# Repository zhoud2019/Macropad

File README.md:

# Macropad

A compact 9-key macropad with 2 rotary encoders, programmed with QMK firmware. I built this project to challenge myself and gain hands-on experience with PCB design, firmware configuration, and hardware assembly, serving as a foundation for more advanced future projects, such as designing a miniature fan in the shape of a plane engine.

The macropad is designed as a programmable input device suitable for shortcuts, media control, and custom workflows.

---

## Overview

---

## Schematic

The schematic shows the wiring between the Seeed XIAO RP2040 microcontroller, the 3×3 switch matrix with 1N4148 diodes, and the two EC11 rotary encoders.

---

## PCB Design

The PCB is a custom 2-layer board designed in KiCad. The switch matrix is arranged in a 3×3 grid with diodes for each key to prevent ghosting. The two rotary encoders are mounted at the top of the board on either side of the XIAO.

Front copper layer:

Back copper layer:

---

## Case Assembly

The enclosure is a 3D-printed case secured with M3 brass heat-set inserts and M3 × 16 mm screws. The case is designed to hold the PCB snugly while keeping the switches and encoders accessible from the top.

---

## Bill of Materials

| Component | Quantity | Part |
|---|---|---|
| Microcontroller | 1x | Seeed XIAO RP2040 |
| Mechanical Switches | 9x | MX-style switches |
| Keycaps | 9x | ABS Keycaps |
| Rotary Encoder | 2x | EC11 |
| Diodes | 9x | 1N4148 |
| Brass Heat-Set Inserts | 4x | M3 |
| Screws | 4x | M3 × 16 mm |
| PCB | 1x | Custom 2-layer PCB |
| Case | 1x | 3D-printed enclosure |

---

## Firmware

This macropad runs [QMK Firmware](https://qmk.fm/). The default keymap assigns keys 1–9 to the switch matrix. The left encoder controls page up/down and the right encoder controls volume up/down.

To flash the firmware:
1. Hold the **BOOT** button on the XIAO and plug it into your computer via USB
2. A drive called **RPI-RP2** will appear
3. Drag and drop `firmware.uf2` onto that drive
4. The drive will disappear and the macropad will reboot with the new firmware

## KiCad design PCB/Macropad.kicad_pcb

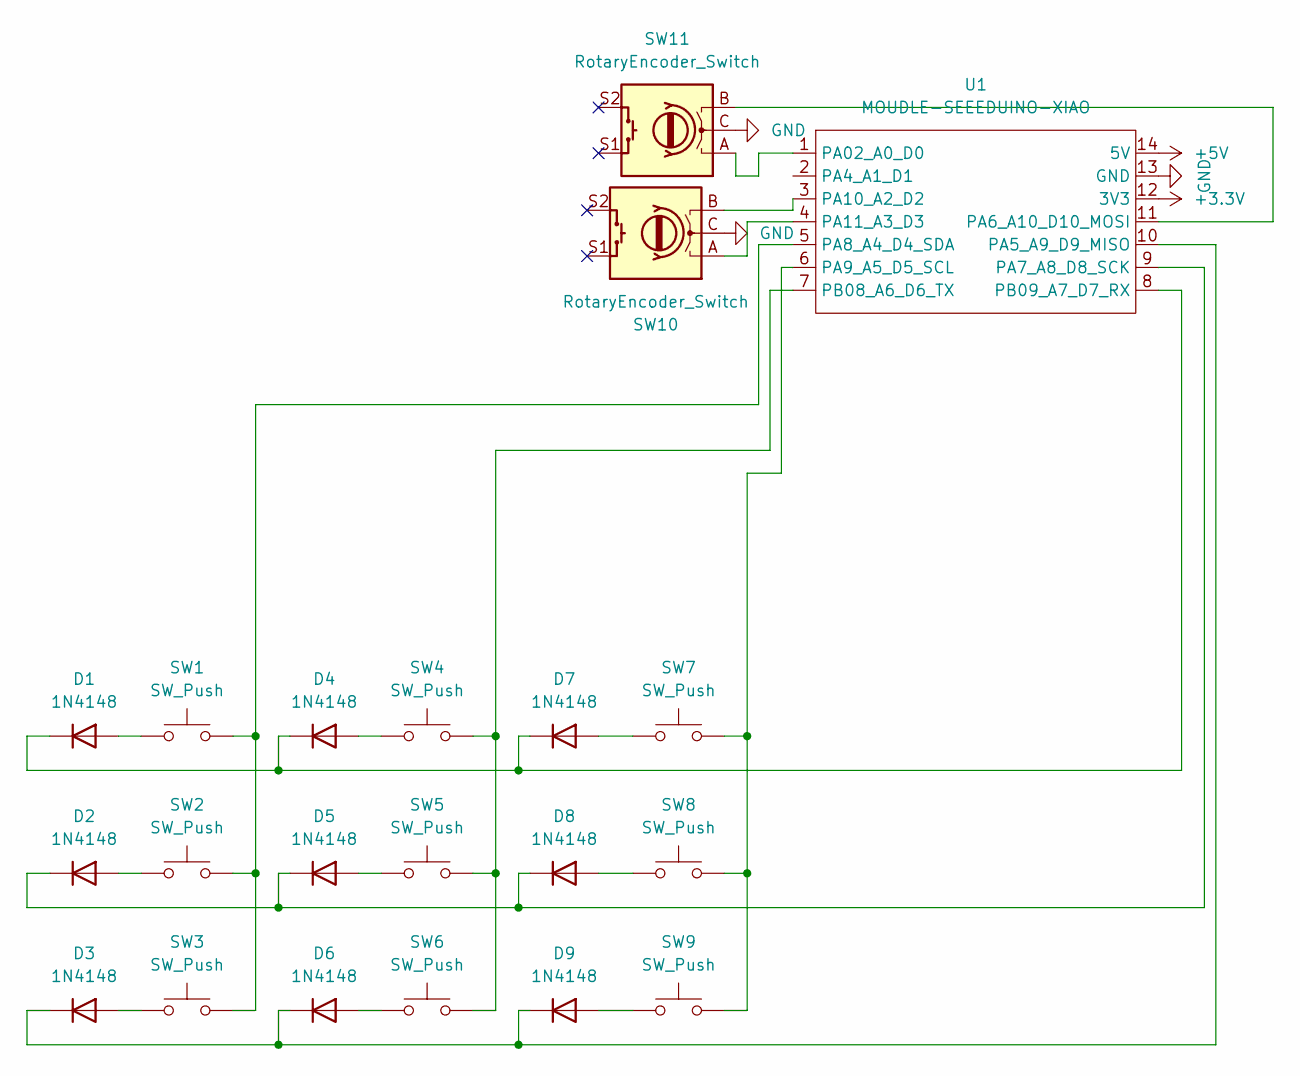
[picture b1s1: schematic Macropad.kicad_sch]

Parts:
D1, D2, D3, D4, D5, D6, D7, D8, D9: 1N4148; D_DO-35_SOD27_P7.62mm_Horizontal
SW1, SW2, SW3, SW4, SW5, SW6, SW7, SW8, SW9: SW_Push; SW_Cherry_MX_1.00u_PCB
SW10, SW11: RotaryEncoder_Switch; RotaryEncoder_Alps_EC11E-Switch_Vertical_H20mm
U1: MOUDLE-SEEEDUINO-XIAO; XIAO-Generic-Hybrid-14P-2.54-21X17.8MM

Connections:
+3.3V: U1.12 (3V3)
+5V: U1.14 (5V)
GND: SW10.C, SW11.C, U1.13 (GND)
unnamed: D1.2 (A), SW1.1
unnamed: D1.1 (K), D4.1 (K), D7.1 (K), U1.8 (PB09_A7_D7_RX)
unnamed: D2.2 (A), SW2.1
unnamed: D2.1 (K), D5.1 (K), D8.1 (K), U1.9 (PA7_A8_D8_SCK)
unnamed: D3.2 (A), SW3.1
unnamed: D3.1 (K), D6.1 (K), D9.1 (K), U1.10 (PA5_A9_D9_MISO)
unnamed: D4.2 (A), SW4.1
unnamed: D5.2 (A), SW5.1
unnamed: D6.2 (A), SW6.1
unnamed: D7.2 (A), SW7.1
unnamed: D8.2 (A), SW8.1
unnamed: D9.2 (A), SW9.1
unnamed: SW11.A, U1.1 (PA02_A0_D0)
unnamed: SW11.B, U1.11 (PA6_A10_D10_MOSI)
unnamed: SW1.2, SW2.2, SW3.2, U1.5 (PA8_A4_D4_SDA)
unnamed: SW7.2, SW8.2, SW9.2, U1.6 (PA9_A5_D5_SCL)
unnamed: SW10.B, U1.3 (PA10_A2_D2)
unnamed: SW10.A, U1.4 (PA11_A3_D3)
unnamed: SW4.2, SW5.2, SW6.2, U1.7 (PB08_A6_D6_TX)

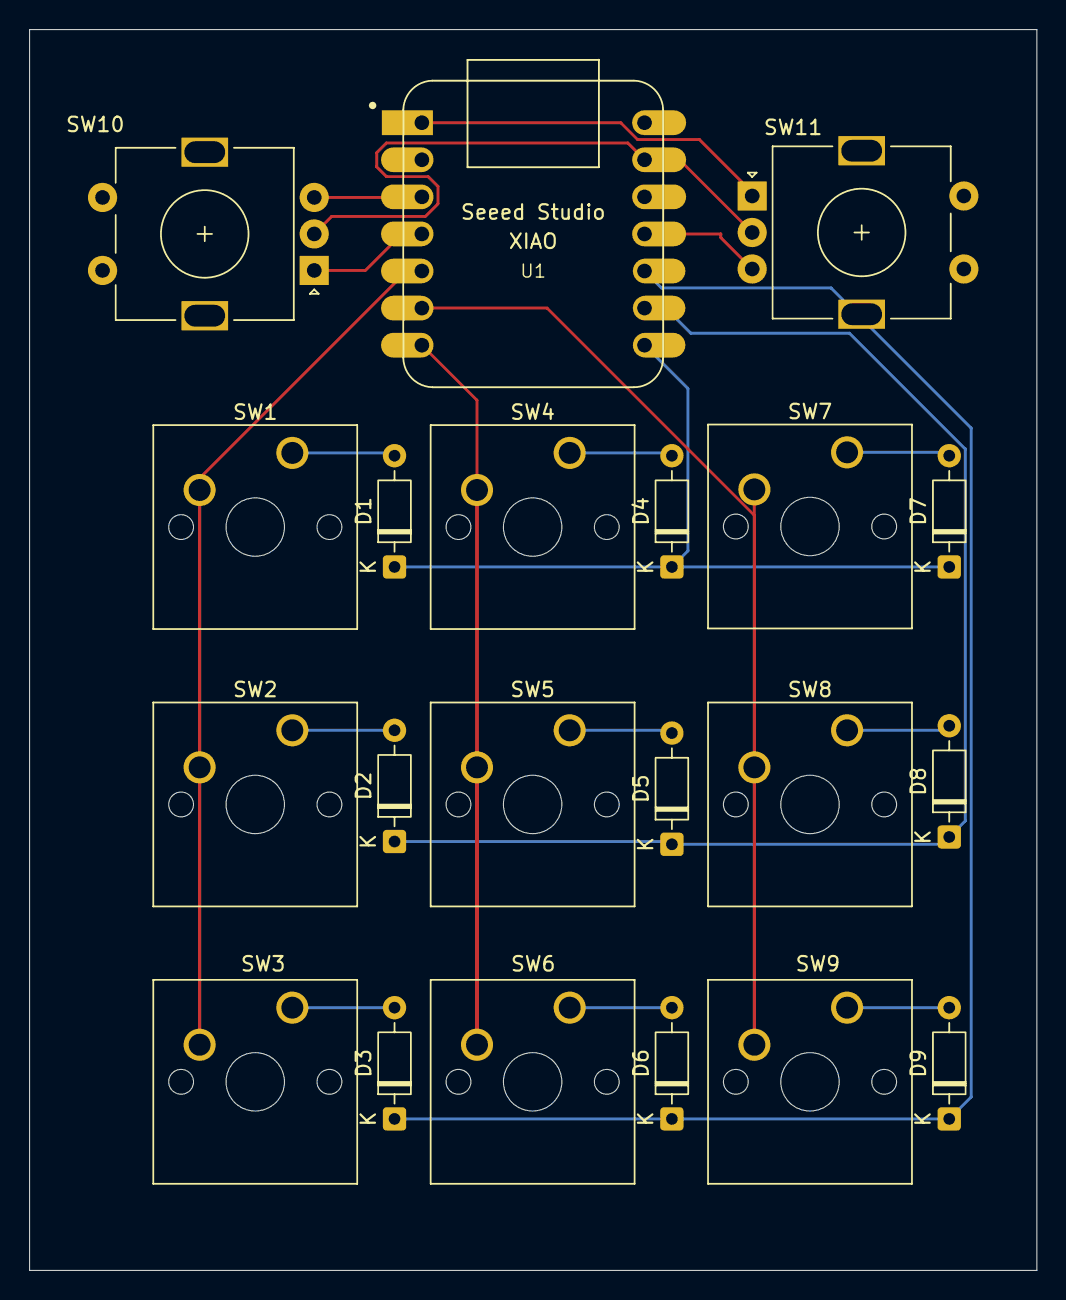
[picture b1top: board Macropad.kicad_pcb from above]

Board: 2 copper layers, 69.0 x 85.0 mm, 21 parts (0 on the bottom side), 20 nets.

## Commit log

2026-03-29 Organized all of the files
